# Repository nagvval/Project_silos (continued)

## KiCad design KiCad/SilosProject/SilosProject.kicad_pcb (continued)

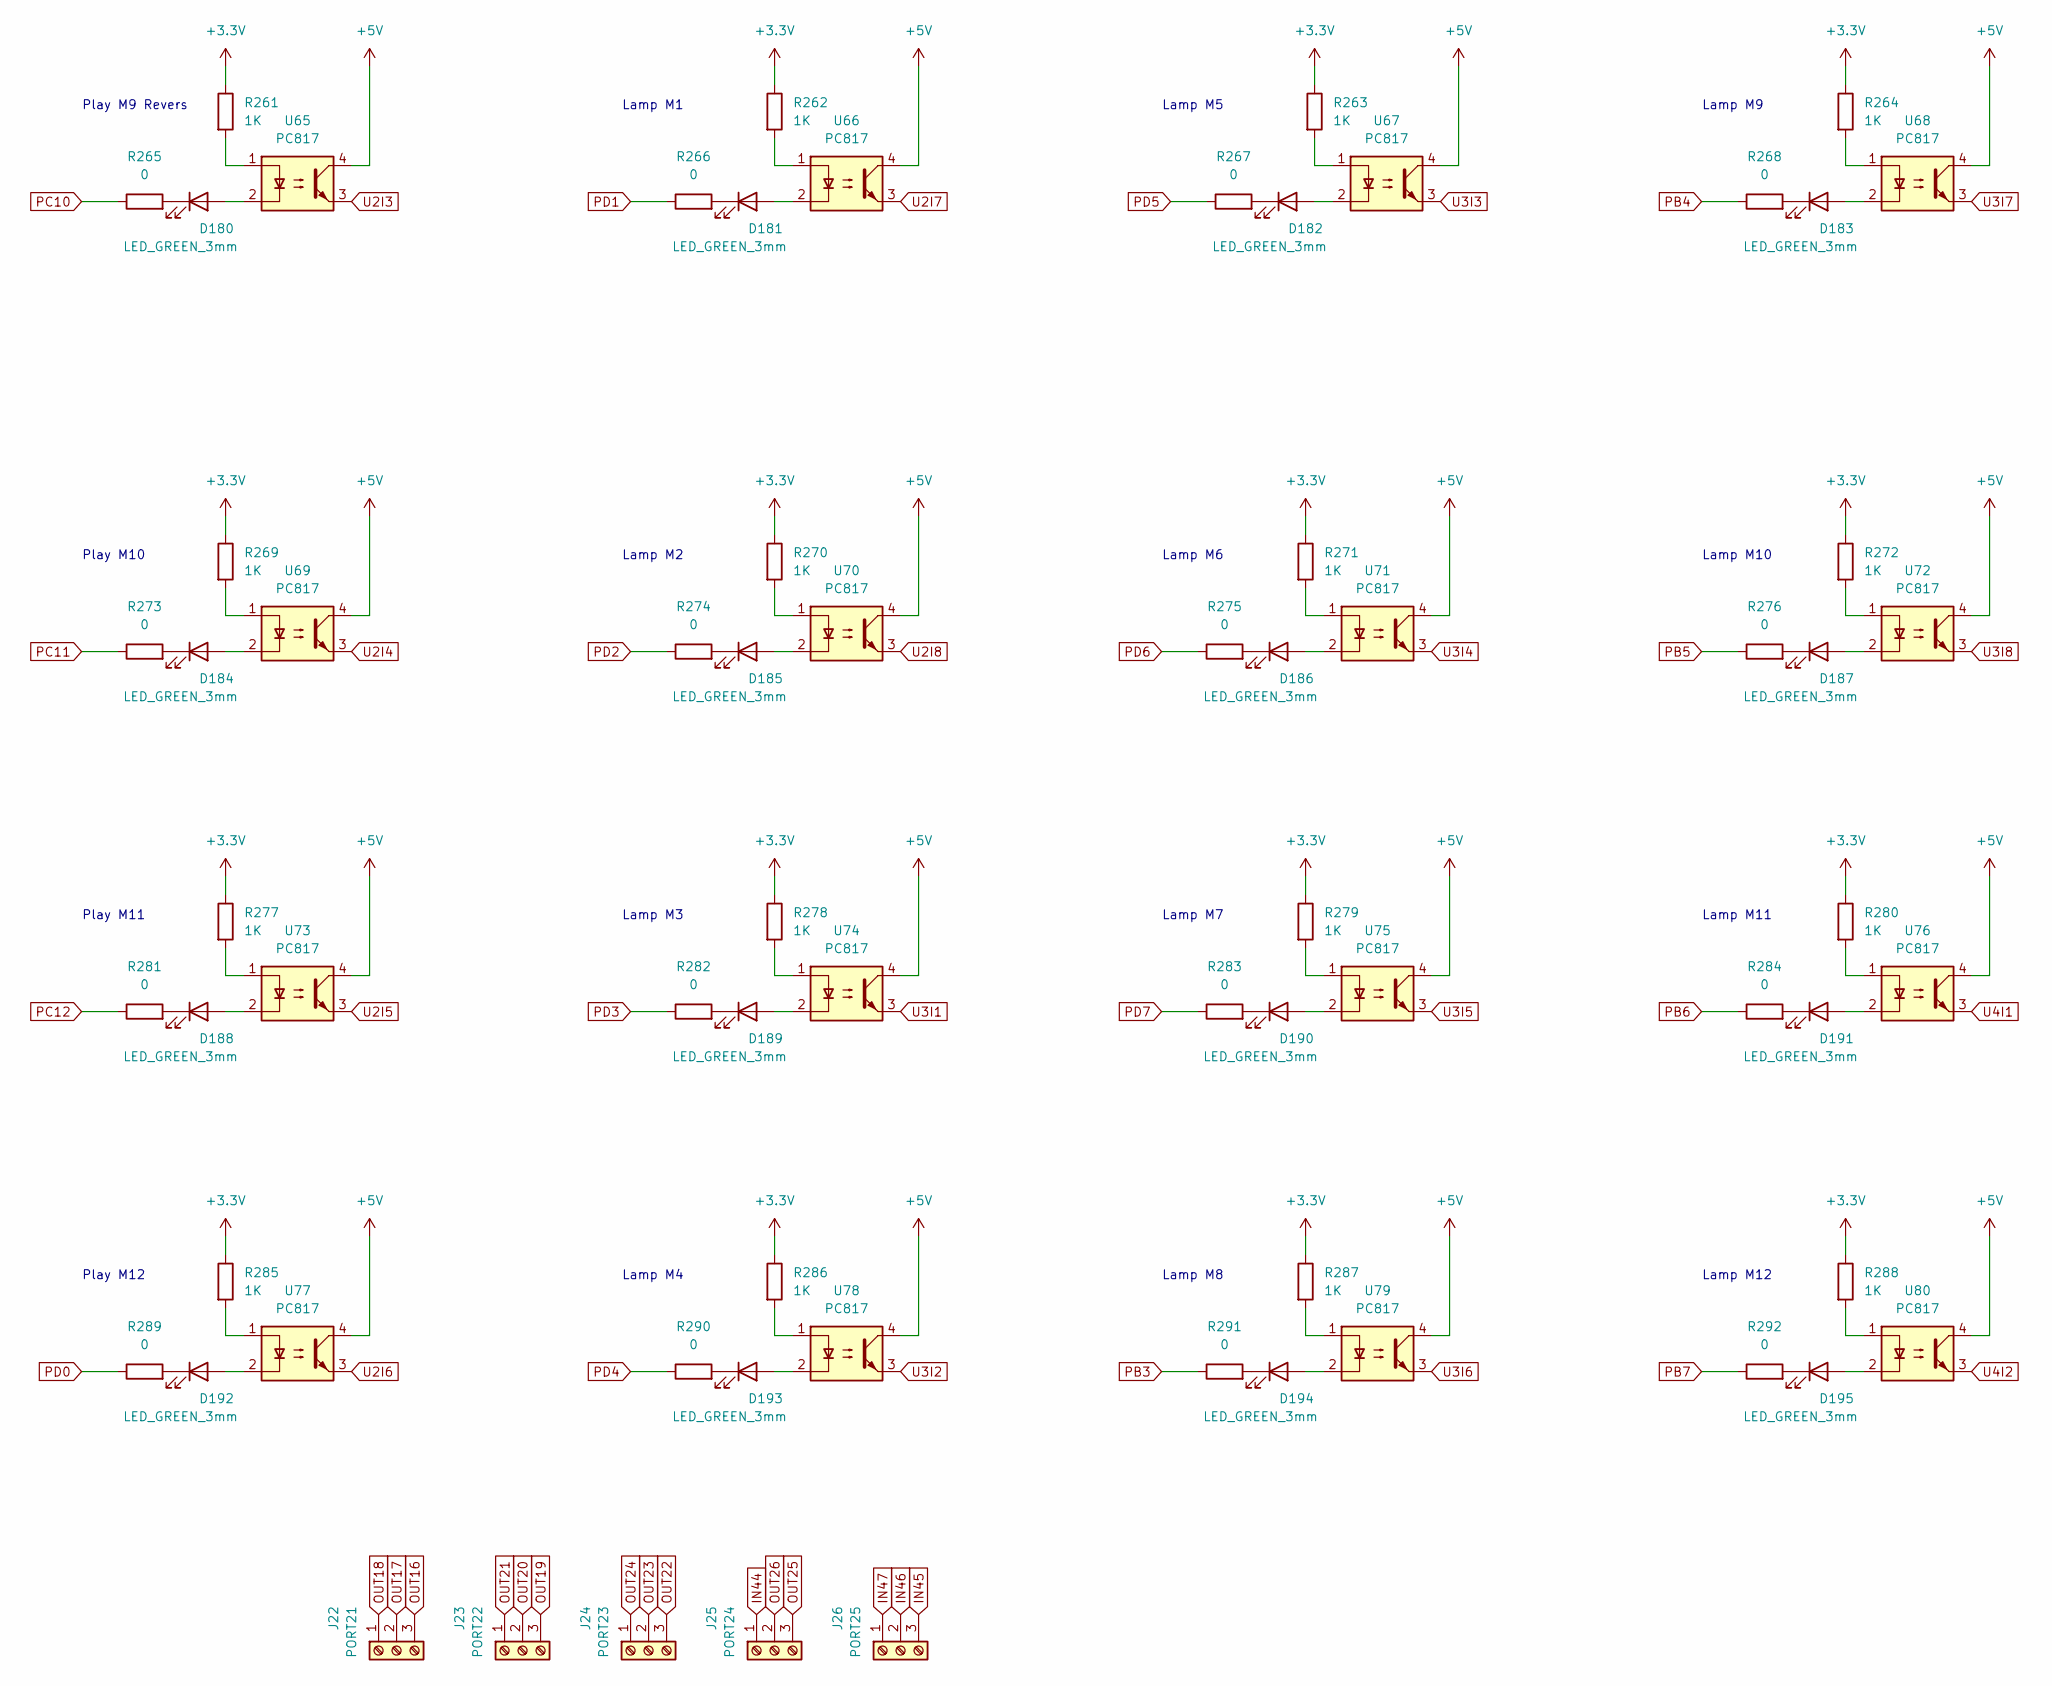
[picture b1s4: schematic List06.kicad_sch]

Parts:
D180, D181, D182, D183, D184, D185, D186, D187, D188, D189, D190, D191, D192, D193, D194, D195: LED_GREEN_3mm; LED_D3.0mm
J22: PORT21; DG306-5.0-03P-12-00A
J23: PORT22; DG306-5.0-03P-12-00A
J24: PORT23; DG306-5.0-03P-12-00A
J25: PORT24; DG306-5.0-03P-12-00A
J26: PORT25; DG306-5.0-03P-12-00A
R261, R262, R263, R264, R269, R270, R271, R272, R277, R278, R279, R280, R285, R286, R287, R288: 1K; R_0805_2012Metric
R265, R266, R267, R268, R273, R274, R275, R276, R281, R282, R283, R284, R289, R290, R291, R292: 0; R_0805_2012Metric
U65, U66, U67, U68, U69, U70, U71, U72, U73, U74, U75, U76, U77, U78, U79, U80: PC817; DIP-4_W7.62mm

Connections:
+3.3V: R261.1, R262.1, R263.1, R264.1, R269.1, R270.1, R271.1, R272.1, R277.1, R278.1, R279.1, R280.1, R285.1, R286.1, R287.1, R288.1; also elsewhere on the board
+5V: U65.4, U66.4, U67.4, U68.4, U69.4, U70.4, U71.4, U72.4, U73.4, U74.4, U75.4, U76.4, U77.4, U78.4, U79.4, U80.4; also elsewhere on the board
IN44: J25.1; also elsewhere on the board
IN45: J26.3; also elsewhere on the board
IN46: J26.2; also elsewhere on the board
IN47: J26.1; also elsewhere on the board
unnamed: D180.1 (K), R265.2
unnamed: D180.2 (A), U65.2
unnamed: D181.1 (K), R266.2
unnamed: D181.2 (A), U66.2
unnamed: D182.1 (K), R267.2
unnamed: D182.2 (A), U67.2
unnamed: D183.1 (K), R268.2
unnamed: D183.2 (A), U68.2
unnamed: D184.1 (K), R273.2
unnamed: D184.2 (A), U69.2
unnamed: D185.1 (K), R274.2
unnamed: D185.2 (A), U70.2
unnamed: D186.1 (K), R275.2
unnamed: D186.2 (A), U71.2
unnamed: D187.1 (K), R276.2
unnamed: D187.2 (A), U72.2
unnamed: D188.1 (K), R281.2
unnamed: D188.2 (A), U73.2
unnamed: D189.1 (K), R282.2
unnamed: D189.2 (A), U74.2
unnamed: D190.1 (K), R283.2
unnamed: D190.2 (A), U75.2
unnamed: D191.1 (K), R284.2
unnamed: D191.2 (A), U76.2
unnamed: D192.1 (K), R289.2
unnamed: D192.2 (A), U77.2
unnamed: D193.1 (K), R290.2
unnamed: D193.2 (A), U78.2
unnamed: D194.1 (K), R291.2
unnamed: D194.2 (A), U79.2
unnamed: D195.1 (K), R292.2
unnamed: D195.2 (A), U80.2
unnamed: R261.2, U65.1
unnamed: R262.2, U66.1
unnamed: R263.2, U67.1
unnamed: R264.2, U68.1
unnamed: R269.2, U69.1
unnamed: R270.2, U70.1
unnamed: R271.2, U71.1
unnamed: R272.2, U72.1
unnamed: R277.2, U73.1
unnamed: R278.2, U74.1
unnamed: R279.2, U75.1
unnamed: R280.2, U76.1
unnamed: R285.2, U77.1
unnamed: R286.2, U78.1
unnamed: R287.2, U79.1
unnamed: R288.2, U80.1
OUT16: J22.3; also elsewhere on the board
OUT17: J22.2; also elsewhere on the board
OUT18: J22.1; also elsewhere on the board
OUT19: J23.3; also elsewhere on the board
OUT20: J23.2; also elsewhere on the board
OUT21: J23.1; also elsewhere on the board
OUT22: J24.3; also elsewhere on the board
OUT23: J24.2; also elsewhere on the board
OUT24: J24.1; also elsewhere on the board
OUT25: J25.3; also elsewhere on the board
OUT26: J25.2; also elsewhere on the board
PB3: R291.1; also elsewhere on the board
PB4: R268.1; also elsewhere on the board
PB5: R276.1; also elsewhere on the board
PB6: R284.1; also elsewhere on the board
PB7: R292.1; also elsewhere on the board
PC10: R265.1; also elsewhere on the board
PC11: R273.1; also elsewhere on the board
PC12: R281.1; also elsewhere on the board
PD0: R289.1; also elsewhere on the board
PD1: R266.1; also elsewhere on the board
PD2: R274.1; also elsewhere on the board
PD3: R282.1; also elsewhere on the board
PD4: R290.1; also elsewhere on the board
PD5: R267.1; also elsewhere on the board
PD6: R275.1; also elsewhere on the board
PD7: R283.1; also elsewhere on the board
U2I3: U65.3; also elsewhere on the board
U2I4: U69.3; also elsewhere on the board
U2I5: U73.3; also elsewhere on the board
U2I6: U77.3; also elsewhere on the board
U2I7: U66.3; also elsewhere on the board
U2I8: U70.3; also elsewhere on the board
U3I1: U74.3; also elsewhere on the board
U3I2: U78.3; also elsewhere on the board
U3I3: U67.3; also elsewhere on the board
U3I4: U71.3; also elsewhere on the board
U3I5: U75.3; also elsewhere on the board
U3I6: U79.3; also elsewhere on the board
U3I7: U68.3; also elsewhere on the board
U3I8: U72.3; also elsewhere on the board
U4I1: U76.3; also elsewhere on the board
U4I2: U80.3; also elsewhere on the board

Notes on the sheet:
Lamp M5
Lamp M12
Play M12
Lamp M1
Lamp M2
Lamp M10
Lamp M3
Lamp M6
Play M9 Revers
Lamp M4
Play M11
Lamp M7
Lamp M9
Lamp M11
Lamp M8
Play M10

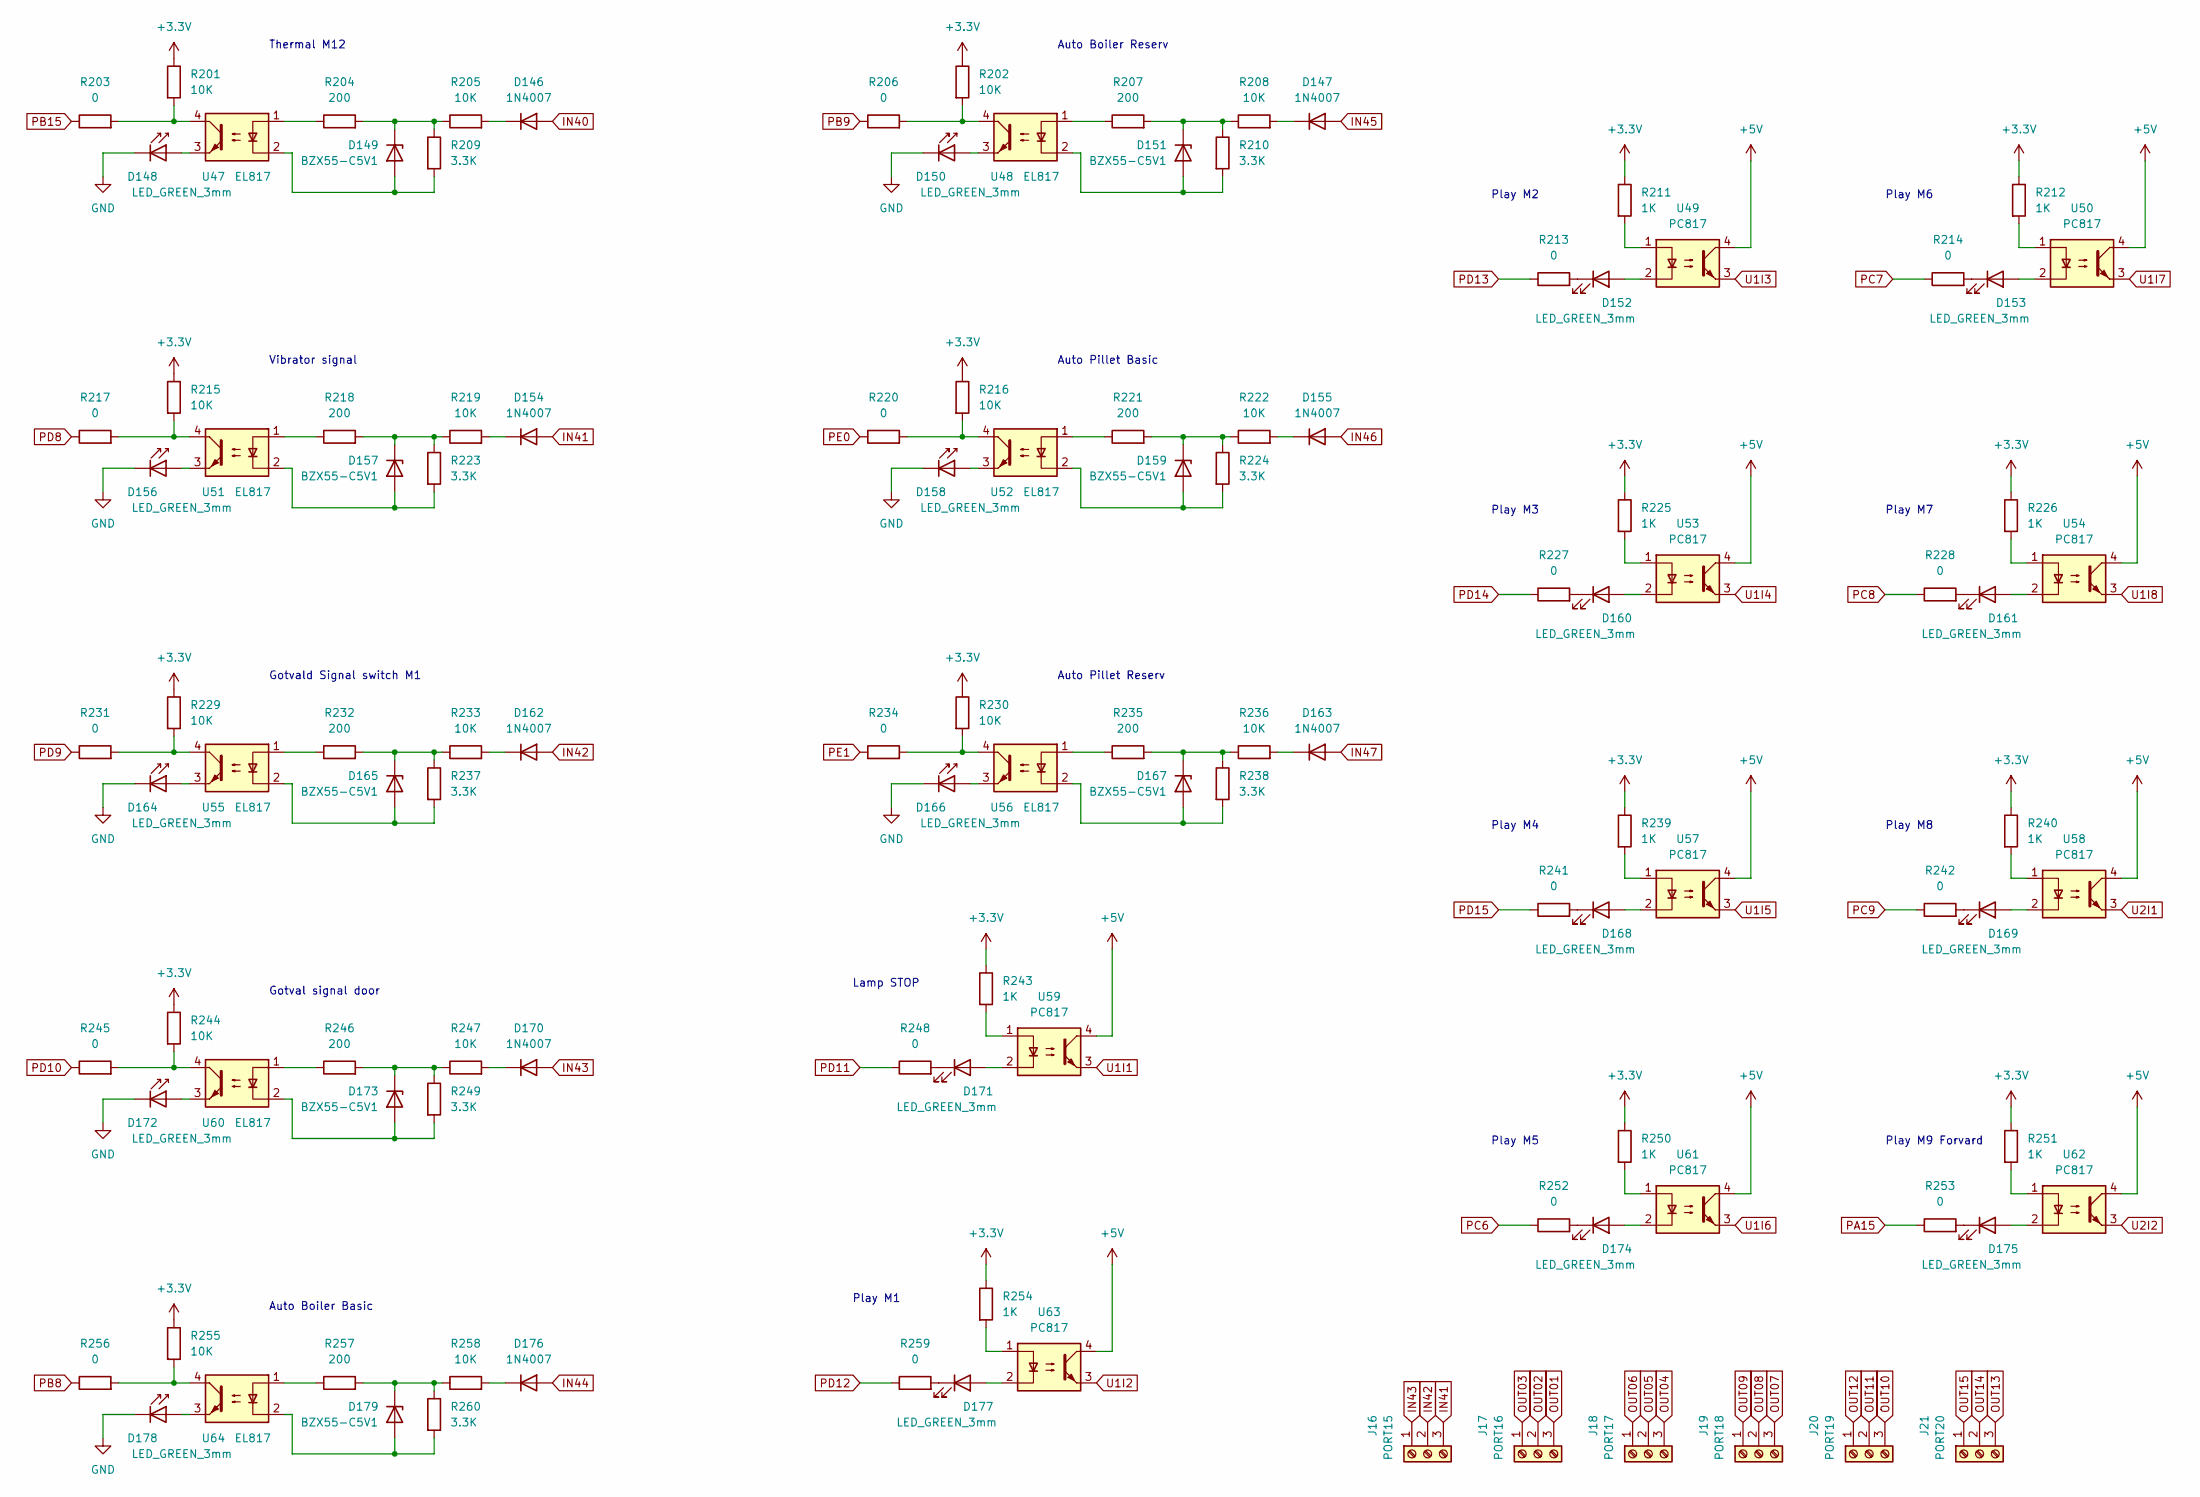
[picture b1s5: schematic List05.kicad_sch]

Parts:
D146, D147, D154, D155, D162, D163, D170, D176: 1N4007; D_DO-41_SOD81_P10.16mm_Horizontal
D148, D150, D152, D153, D156, D158, D160, D161, D164, D166, D168, D169, D171, D172, D174, D175, D177, D178: LED_GREEN_3mm; LED_D3.0mm
D149, D151, D157, D159, D165, D167, D173, D179: BZX55-C5V1; D_DO-35_SOD27_P2.54mm_Vertical_AnodeUp
J16: PORT15; DG306-5.0-03P-12-00A
J17: PORT16; DG306-5.0-03P-12-00A
J18: PORT17; DG306-5.0-03P-12-00A
J19: PORT18; DG306-5.0-03P-12-00A
J20: PORT19; DG306-5.0-03P-12-00A
J21: PORT20; DG306-5.0-03P-12-00A
R201, R202, R215, R216, R229, R230, R244, R255: 10K; R_0805_2012Metric
R203, R206, R213, R214, R217, R220, R227, R228, R231, R234, R241, R242, R245, R248, R252, R253, R256, R259: 0; R_0805_2012Metric
R204, R207, R218, R221, R232, R235, R246, R257: 200; R_0805_2012Metric
R205, R208, R219, R222, R233, R236, R247, R258: 10K; R_2512_6332Metric
R209, R210, R223, R224, R237, R238, R249, R260: 3.3K; R_1206_3216Metric
R211, R212, R225, R226, R239, R240, R243, R250, R251, R254: 1K; R_0805_2012Metric
U47, U48, U51, U52, U55, U56, U60, U64: EL817; DIP-4_W7.62mm
U49, U50, U53, U54, U57, U58, U59, U61, U62, U63: PC817; DIP-4_W7.62mm

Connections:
+3.3V: R201.1, R202.1, R211.1, R212.1, R215.1, R216.1, R225.1, R226.1, R229.1, R230.1, R239.1, R240.1, R243.1, R244.1, R250.1, R251.1, R254.1, R255.1; also elsewhere on the board
+5V: U49.4, U50.4, U53.4, U54.4, U57.4, U58.4, U59.4, U61.4, U62.4, U63.4; also elsewhere on the board
GND: D148.1 (K), D150.1 (K), D156.1 (K), D158.1 (K), D164.1 (K), D166.1 (K), D172.1 (K), D178.1 (K); also elsewhere on the board
IN40: D146.2 (A); also elsewhere on the board
IN41: D154.2 (A), J16.3
IN42: D162.2 (A), J16.2
IN43: D170.2 (A), J16.1
IN44: D176.2 (A); also elsewhere on the board
IN45: D147.2 (A); also elsewhere on the board
IN46: D155.2 (A); also elsewhere on the board
IN47: D163.2 (A); also elsewhere on the board
unnamed: D146.1 (K), R205.2
unnamed: D147.1 (K), R208.2
unnamed: D148.2 (A), U47.3
unnamed: D149.1 (K), R204.2, R205.1, R209.1
unnamed: D149.2 (A), R209.2, U47.2
unnamed: D150.2 (A), U48.3
unnamed: D151.1 (K), R207.2, R208.1, R210.1
unnamed: D151.2 (A), R210.2, U48.2
unnamed: D152.1 (K), R213.2
unnamed: D152.2 (A), U49.2
unnamed: D153.1 (K), R214.2
unnamed: D153.2 (A), U50.2
unnamed: D154.1 (K), R219.2
unnamed: D155.1 (K), R222.2
unnamed: D156.2 (A), U51.3
unnamed: D157.1 (K), R218.2, R219.1, R223.1
unnamed: D157.2 (A), R223.2, U51.2
unnamed: D158.2 (A), U52.3
unnamed: D159.1 (K), R221.2, R222.1, R224.1
unnamed: D159.2 (A), R224.2, U52.2
unnamed: D160.1 (K), R227.2
unnamed: D160.2 (A), U53.2
unnamed: D161.1 (K), R228.2
unnamed: D161.2 (A), U54.2
unnamed: D162.1 (K), R233.2
unnamed: D163.1 (K), R236.2
unnamed: D164.2 (A), U55.3
unnamed: D165.1 (K), R232.2, R233.1, R237.1
unnamed: D165.2 (A), R237.2, U55.2
unnamed: D166.2 (A), U56.3
unnamed: D167.1 (K), R235.2, R236.1, R238.1
unnamed: D167.2 (A), R238.2, U56.2
unnamed: D168.1 (K), R241.2
unnamed: D168.2 (A), U57.2
unnamed: D169.1 (K), R242.2
unnamed: D169.2 (A), U58.2
unnamed: D170.1 (K), R247.2
unnamed: D171.1 (K), R248.2
unnamed: D171.2 (A), U59.2
unnamed: D172.2 (A), U60.3
unnamed: D173.1 (K), R246.2, R247.1, R249.1
unnamed: D173.2 (A), R249.2, U60.2
unnamed: D174.1 (K), R252.2
unnamed: D174.2 (A), U61.2
unnamed: D175.1 (K), R253.2
unnamed: D175.2 (A), U62.2
unnamed: D176.1 (K), R258.2
unnamed: D177.1 (K), R259.2
unnamed: D177.2 (A), U63.2
unnamed: D178.2 (A), U64.3
unnamed: D179.1 (K), R257.2, R258.1, R260.1
unnamed: D179.2 (A), R260.2, U64.2
unnamed: R201.2, R203.2, U47.4
unnamed: R202.2, R206.2, U48.4
unnamed: R204.1, U47.1
unnamed: R207.1, U48.1
unnamed: R211.2, U49.1
unnamed: R212.2, U50.1
unnamed: R215.2, R217.2, U51.4
unnamed: R216.2, R220.2, U52.4
unnamed: R218.1, U51.1
unnamed: R221.1, U52.1
unnamed: R225.2, U53.1
unnamed: R226.2, U54.1
unnamed: R229.2, R231.2, U55.4
unnamed: R230.2, R234.2, U56.4
unnamed: R232.1, U55.1
unnamed: R235.1, U56.1
unnamed: R239.2, U57.1
unnamed: R240.2, U58.1
unnamed: R243.2, U59.1
unnamed: R244.2, R245.2, U60.4
unnamed: R246.1, U60.1
unnamed: R250.2, U61.1
unnamed: R251.2, U62.1
unnamed: R254.2, U63.1
unnamed: R255.2, R256.2, U64.4
unnamed: R257.1, U64.1
OUT01: J17.3; also elsewhere on the board
OUT02: J17.2; also elsewhere on the board
OUT03: J17.1; also elsewhere on the board
OUT04: J18.3; also elsewhere on the board
OUT05: J18.2; also elsewhere on the board
OUT06: J18.1; also elsewhere on the board
OUT07: J19.3; also elsewhere on the board
OUT08: J19.2; also elsewhere on the board
OUT09: J19.1; also elsewhere on the board
OUT10: J20.3; also elsewhere on the board
OUT11: J20.2; also elsewhere on the board
OUT12: J20.1; also elsewhere on the board
OUT13: J21.3; also elsewhere on the board
OUT14: J21.2; also elsewhere on the board
OUT15: J21.1; also elsewhere on the board
PA15: R253.1; also elsewhere on the board
PB8: R256.1; also elsewhere on the board
PB9: R206.1; also elsewhere on the board
PB15: R203.1; also elsewhere on the board
PC6: R252.1; also elsewhere on the board
PC7: R214.1; also elsewhere on the board
PC8: R228.1; also elsewhere on the board
PC9: R242.1; also elsewhere on the board
PD8: R217.1; also elsewhere on the board
PD9: R231.1; also elsewhere on the board
PD10: R245.1; also elsewhere on the board
PD11: R248.1; also elsewhere on the board
PD12: R259.1; also elsewhere on the board
PD13: R213.1; also elsewhere on the board
PD14: R227.1; also elsewhere on the board
PD15: R241.1; also elsewhere on the board
PE0: R220.1; also elsewhere on the board
PE1: R234.1; also elsewhere on the board
U1I1: U59.3; also elsewhere on the board
U1I2: U63.3; also elsewhere on the board
U1I3: U49.3; also elsewhere on the board
U1I4: U53.3; also elsewhere on the board
U1I5: U57.3; also elsewhere on the board
U1I6: U61.3; also elsewhere on the board
U1I7: U50.3; also elsewhere on the board
U1I8: U54.3; also elsewhere on the board
U2I1: U58.3; also elsewhere on the board
U2I2: U62.3; also elsewhere on the board

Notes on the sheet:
Vibrator signal
Play M3
Play M2
Play M7
Play M1
Gotvald Signal switch M1
Play M8
Play M4
Play M9 Forvard
Auto Pillet Basic
Auto Boiler Basic
Lamp STOP
Auto Pillet Reserv
Gotval signal door
Auto Boiler Reserv
Play M6
Play M5
Thermal M12

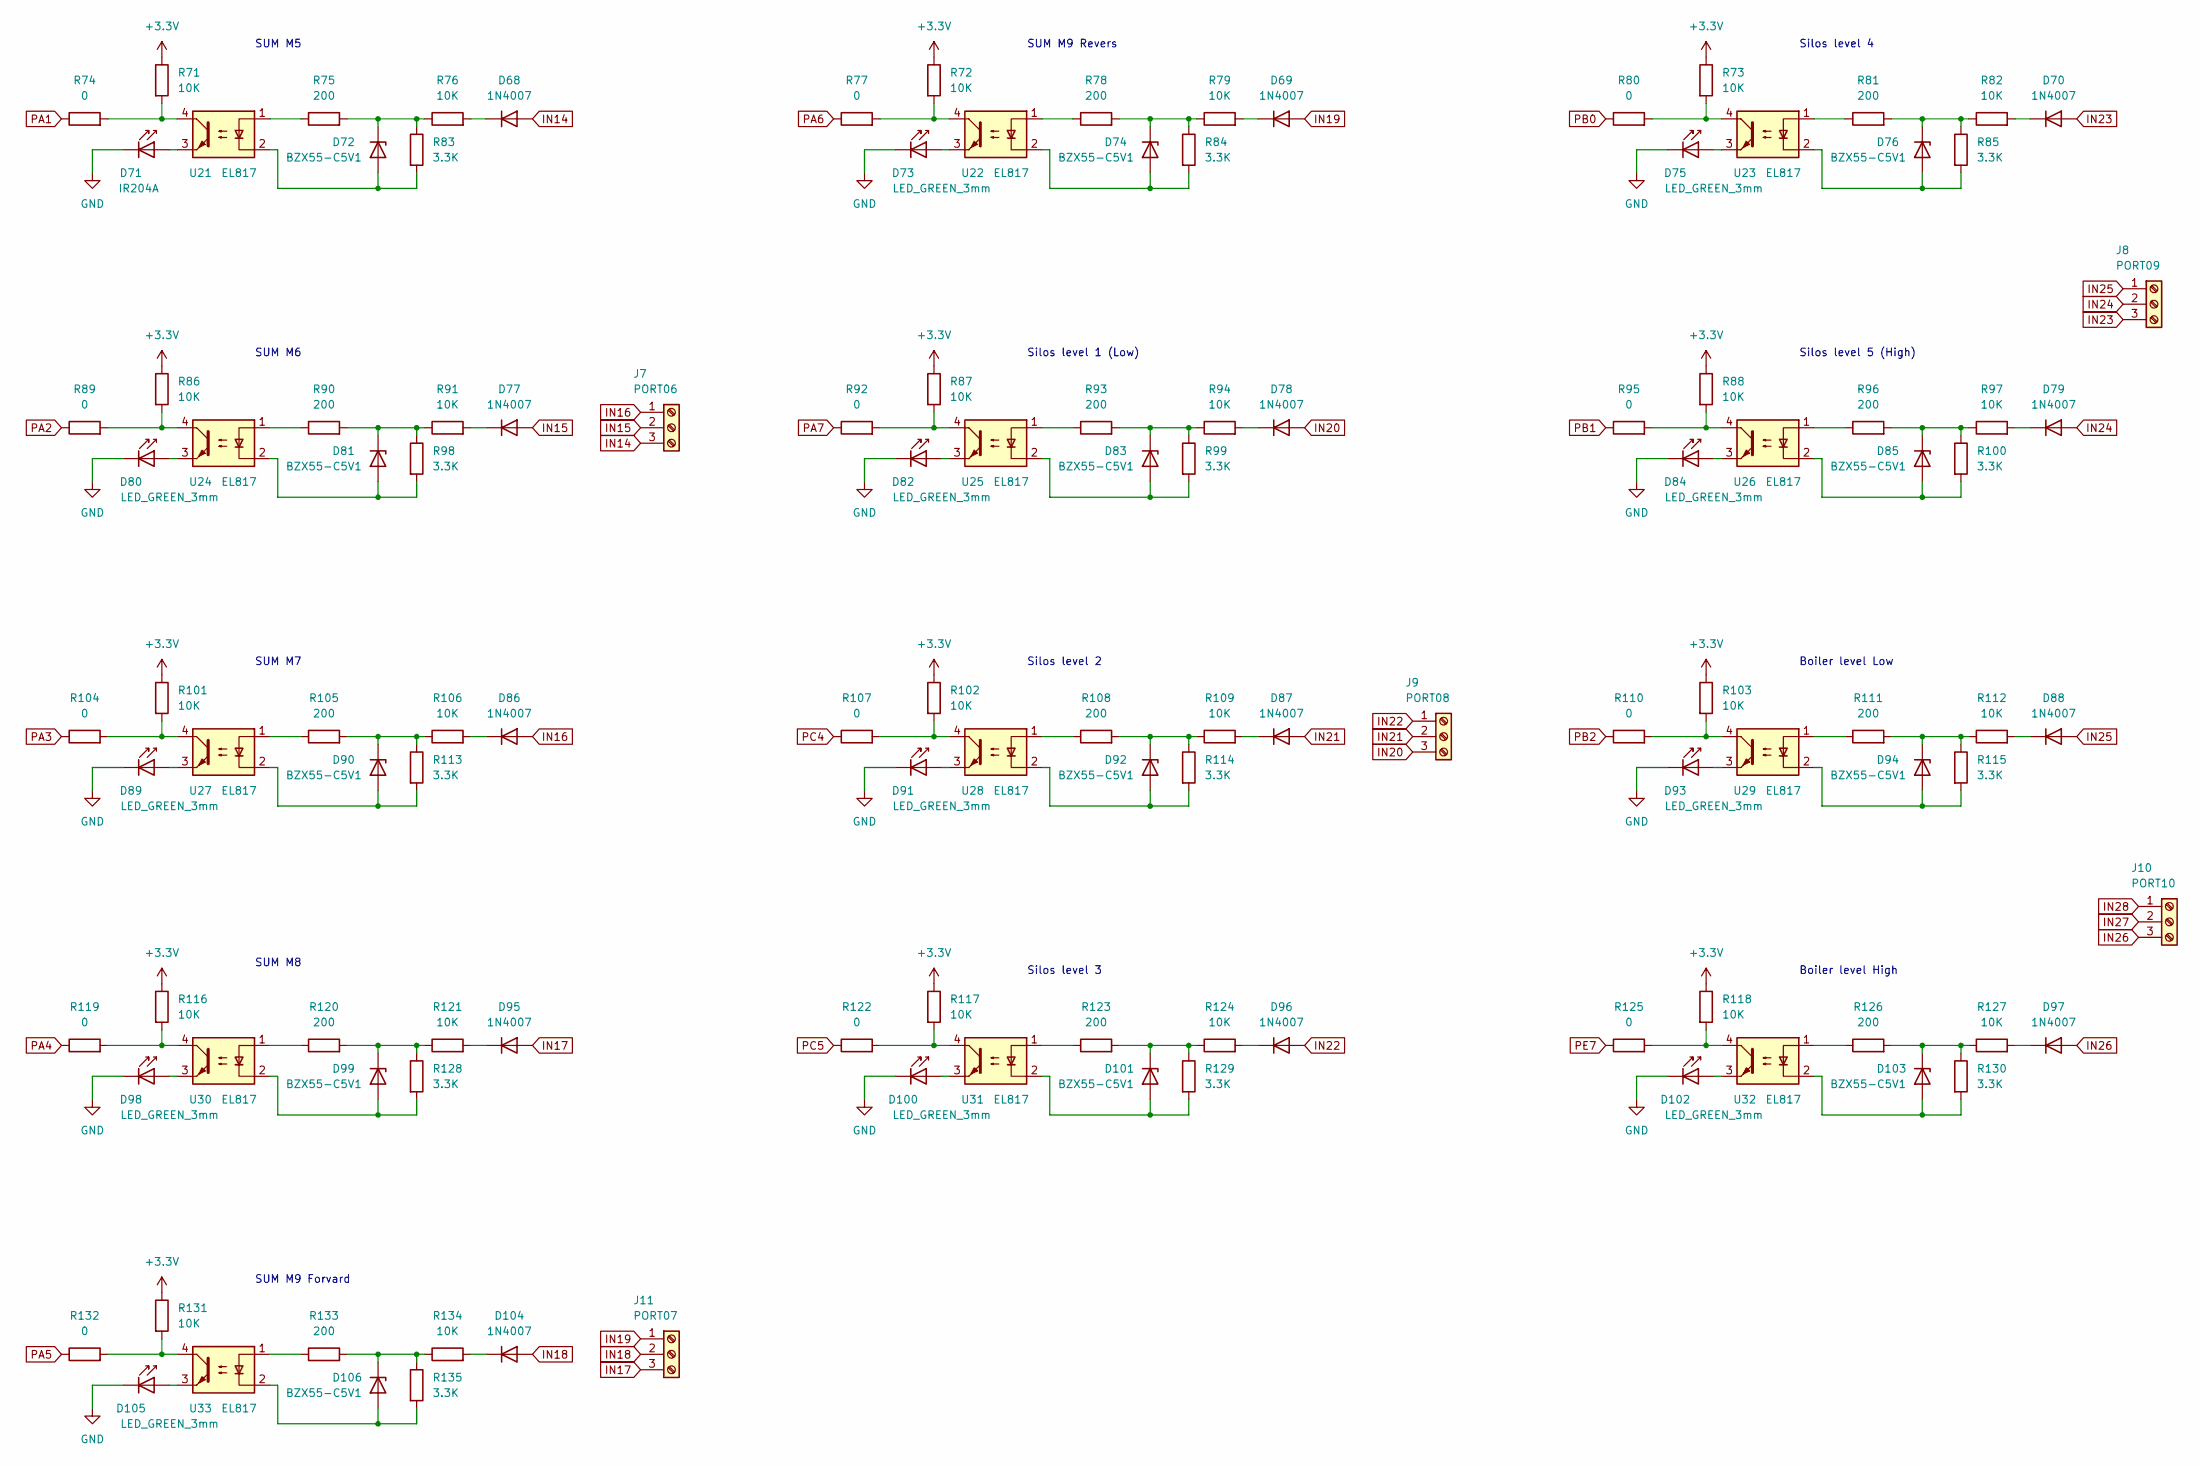
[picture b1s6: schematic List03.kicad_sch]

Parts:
D68, D69, D70, D77, D78, D79, D86, D87, D88, D95, D96, D97, D104: 1N4007; D_DO-41_SOD81_P10.16mm_Horizontal
D71: IR204A; LED_D3.0mm_IRBlack
D72, D74, D76, D81, D83, D85, D90, D92, D94, D99, D101, D103, D106: BZX55-C5V1; D_DO-35_SOD27_P2.54mm_Vertical_AnodeUp
D73, D75, D80, D82, D84, D89, D91, D93, D98, D100, D102, D105: LED_GREEN_3mm; LED_D3.0mm
J7: PORT06; DG306-5.0-03P-12-00A
J8: PORT09; DG306-5.0-03P-12-00A
J9: PORT08; DG306-5.0-03P-12-00A
J10: PORT10; DG306-5.0-03P-12-00A
J11: PORT07; DG306-5.0-03P-12-00A
R71, R72, R73, R86, R87, R88, R101, R102, R103, R116, R117, R118, R131: 10K; R_0805_2012Metric
R74, R77, R80, R89, R92, R95, R104, R107, R110, R119, R122, R125, R132: 0; R_0805_2012Metric
R75, R78, R81, R90, R93, R96, R105, R108, R111, R120, R123, R126, R133: 200; R_0805_2012Metric
R76, R79, R82, R91, R94, R97, R106, R109, R112, R121, R124, R127, R134: 10K; R_2512_6332Metric
R83, R84, R85, R98, R99, R100, R113, R114, R115, R128, R129, R130, R135: 3.3K; R_1206_3216Metric
U21, U22, U23, U24, U25, U26, U27, U28, U29, U30, U31, U32, U33: EL817; DIP-4_W7.62mm

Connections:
+3.3V: R71.1, R72.1, R73.1, R86.1, R87.1, R88.1, R101.1, R102.1, R103.1, R116.1, R117.1, R118.1, R131.1; also elsewhere on the board
GND: D71.1 (K), D73.1 (K), D75.1 (K), D80.1 (K), D82.1 (K), D84.1 (K), D89.1 (K), D91.1 (K), D93.1 (K), D98.1 (K), D100.1 (K), D102.1 (K), D105.1 (K); also elsewhere on the board
IN14: D68.2 (A), J7.3
IN15: D77.2 (A), J7.2
IN16: D86.2 (A), J7.1
IN17: D95.2 (A), J11.3
IN18: D104.2 (A), J11.2
IN19: D69.2 (A), J11.1
IN20: D78.2 (A), J9.3
IN21: D87.2 (A), J9.2
IN22: D96.2 (A), J9.1
IN23: D70.2 (A), J8.3
IN24: D79.2 (A), J8.2
IN25: D88.2 (A), J8.1
IN26: D97.2 (A), J10.3
IN27: J10.2; also elsewhere on the board
IN28: J10.1; also elsewhere on the board
unnamed: D68.1 (K), R76.2
unnamed: D69.1 (K), R79.2
unnamed: D70.1 (K), R82.2
unnamed: D71.2 (A), U21.3
unnamed: D72.1 (K), R75.2, R76.1, R83.1
unnamed: D72.2 (A), R83.2, U21.2
unnamed: D73.2 (A), U22.3
unnamed: D74.1 (K), R78.2, R79.1, R84.1
unnamed: D74.2 (A), R84.2, U22.2
unnamed: D75.2 (A), U23.3
unnamed: D76.1 (K), R81.2, R82.1, R85.1
unnamed: D76.2 (A), R85.2, U23.2
unnamed: D77.1 (K), R91.2
unnamed: D78.1 (K), R94.2
unnamed: D79.1 (K), R97.2
unnamed: D80.2 (A), U24.3
unnamed: D81.1 (K), R90.2, R91.1, R98.1
unnamed: D81.2 (A), R98.2, U24.2
unnamed: D82.2 (A), U25.3
unnamed: D83.1 (K), R93.2, R94.1, R99.1
unnamed: D83.2 (A), R99.2, U25.2
unnamed: D84.2 (A), U26.3
unnamed: D85.1 (K), R96.2, R97.1, R100.1
unnamed: D85.2 (A), R100.2, U26.2
unnamed: D86.1 (K), R106.2
unnamed: D87.1 (K), R109.2
unnamed: D88.1 (K), R112.2
unnamed: D89.2 (A), U27.3
unnamed: D90.1 (K), R105.2, R106.1, R113.1
unnamed: D90.2 (A), R113.2, U27.2
unnamed: D91.2 (A), U28.3
unnamed: D92.1 (K), R108.2, R109.1, R114.1
unnamed: D92.2 (A), R114.2, U28.2
unnamed: D93.2 (A), U29.3
unnamed: D94.1 (K), R111.2, R112.1, R115.1
unnamed: D94.2 (A), R115.2, U29.2
unnamed: D95.1 (K), R121.2
unnamed: D96.1 (K), R124.2
unnamed: D97.1 (K), R127.2
unnamed: D98.2 (A), U30.3
unnamed: D99.1 (K), R120.2, R121.1, R128.1
unnamed: D99.2 (A), R128.2, U30.2
unnamed: D100.2 (A), U31.3
unnamed: D101.1 (K), R123.2, R124.1, R129.1
unnamed: D101.2 (A), R129.2, U31.2
unnamed: D102.2 (A), U32.3
unnamed: D103.1 (K), R126.2, R127.1, R130.1
unnamed: D103.2 (A), R130.2, U32.2
unnamed: D104.1 (K), R134.2
unnamed: D105.2 (A), U33.3
unnamed: D106.1 (K), R133.2, R134.1, R135.1
unnamed: D106.2 (A), R135.2, U33.2
unnamed: R71.2, R74.2, U21.4
unnamed: R72.2, R77.2, U22.4
unnamed: R73.2, R80.2, U23.4
unnamed: R75.1, U21.1
unnamed: R78.1, U22.1
unnamed: R81.1, U23.1
unnamed: R86.2, R89.2, U24.4
unnamed: R87.2, R92.2, U25.4
unnamed: R88.2, R95.2, U26.4
unnamed: R90.1, U24.1
unnamed: R93.1, U25.1
unnamed: R96.1, U26.1
unnamed: R101.2, R104.2, U27.4
unnamed: R102.2, R107.2, U28.4
unnamed: R103.2, R110.2, U29.4
unnamed: R105.1, U27.1
unnamed: R108.1, U28.1
unnamed: R111.1, U29.1
unnamed: R116.2, R119.2, U30.4
unnamed: R117.2, R122.2, U31.4
unnamed: R118.2, R125.2, U32.4
unnamed: R120.1, U30.1
unnamed: R123.1, U31.1
unnamed: R126.1, U32.1
unnamed: R131.2, R132.2, U33.4
unnamed: R133.1, U33.1
PA1: R74.1; also elsewhere on the board
PA2: R89.1; also elsewhere on the board
PA3: R104.1; also elsewhere on the board
PA4: R119.1; also elsewhere on the board
PA5: R132.1; also elsewhere on the board
PA6: R77.1; also elsewhere on the board
PA7: R92.1; also elsewhere on the board
PB0: R80.1; also elsewhere on the board
PB1: R95.1; also elsewhere on the board
PB2: R110.1; also elsewhere on the board
PC4: R107.1; also elsewhere on the board
PC5: R122.1; also elsewhere on the board
PE7: R125.1; also elsewhere on the board

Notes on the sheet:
SUM M7
SUM M9 Revers
Boiler level Low
SUM M6
Silos level 3
Silos level 1 (Low)
Silos level 2
SUM M5
SUM M8
Silos level 4
Silos level 5 (High)
SUM M9 Forvard
Boiler level High
